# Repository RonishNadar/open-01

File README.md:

# OPEN-01

**OPEN-01** is an open-source, low-cost differential drive robot platform focused on embedded sensing, motion control, and autonomous navigation.

This repository contains the full stack:
- ESP-IDF firmware for the ESP32-S2 robot controller
- ROS2 serial bridge and bringup for Raspberry Pi 3B
- URDF robot description with STL meshes
- RViz2 visualization stack for the dev laptop
- robot_localization EKF for sensor fusion
- Linux setup scripts for both machines

---

## What this repo is

OPEN-01 is designed as a low-cost, replicable alternative to the TurtleBot3. It is built around proven hardware and a clean layered architecture — embedded-first, with ROS2 as the autonomy layer on top.

The platform is structured around two compute nodes:

- **ESP32-S2** — handles all real-time firmware: sensors, motors, odometry, and UART telemetry
- **Raspberry Pi 3B** — runs ROS2 Humble, bridges ESP32 telemetry to ROS2 topics, and relays lidar data
- **Laptop** — runs EKF, SLAM, Nav2, and RViz2 visualization over WiFi

---

## Current capabilities

### Firmware (ESP32-S2)
- **Motor control** — FIT0441 brushless DC motors, 25kHz PWM, encoder feedback, startup kick
- **IMU** — MPU6500 (WHO_AM_I=0x70), dedicated I2C bus, accel + gyro
- **ToF ranging** — 3x VL53L0X (left, right, back), XSHUT-based address assignment
- **Odometry** — wheel encoder integration, kinematics
- **Battery monitoring** — 3S Li-Ion voltage via ADC with voltage divider
- **UART telemetry** — custom binary protocol at 460800 baud with CRC16-CCITT

### ROS2 Stack (Raspberry Pi 3B — ROS2 Humble)
- **Serial bridge node** — parses ESP32 binary protocol, publishes all sensor topics
- **Lidar node** — LDS-02 lidar via USB2LDS adapter, publishes `/scan` *(in progress)*
- **robot_state_publisher** — broadcasts full TF tree from URDF
- **Systemd autostart** — `open01.service` brings up the full stack on boot

### ROS2 Stack (Laptop — ROS2 Jazzy)
- **RViz2 visualization** — CAD model, TF frames, odometry, lidar scan
- **robot_localization EKF** — fuses `/odom` + `/imu/data` → `/odometry/filtered` at 30Hz
- **SLAM Toolbox** — *(planned)*
- **Nav2** — *(planned)*

### Published ROS2 Topics
| Topic | Type | Source |
|-------|------|--------|
| `/odom` | `nav_msgs/Odometry` | Serial bridge |
| `/imu/data` | `sensor_msgs/Imu` | Serial bridge |
| `/battery_state` | `sensor_msgs/BatteryState` | Serial bridge |
| `/tof/left` | `sensor_msgs/Range` | Serial bridge |
| `/tof/right` | `sensor_msgs/Range` | Serial bridge |
| `/tof/back` | `sensor_msgs/Range` | Serial bridge |
| `/scan` | `sensor_msgs/LaserScan` | Lidar node |
| `/joint_states` | `sensor_msgs/JointState` | Serial bridge |
| `/odometry/filtered` | `nav_msgs/Odometry` | EKF node |
| `/cmd_vel` | `geometry_msgs/Twist` | Nav2 / teleop |

---

## Hardware

| Component | Part |
|-----------|------|
| Microcontroller | ESP32-S2 |
| Companion computer | Raspberry Pi 3B |
| Motors | FIT0441 brushless DC with encoders |
| IMU | MPU6500 |
| ToF sensors | 3x VL53L0X |
| Lidar | LDS-02 (via USB2LDS adapter, CP210x) |
| Battery | 3S Li-Ion (12.6V full, 9.0V cutoff) |

### Pin Map (ESP32-S2)

| Function | GPIO |
|----------|------|
| I2C Bus 0 SDA (ToF) | GPIO14 |
| I2C Bus 0 SCL (ToF) | GPIO13 |
| I2C Bus 1 SDA (IMU) | GPIO5 |
| I2C Bus 1 SCL (IMU) | GPIO4 |
| XSHUT Left (0x30) | GPIO12 |
| XSHUT Back (0x31) | GPIO11 |
| XSHUT Right (0x32) | GPIO10 |
| UART TX | GPIO19 |
| UART RX | GPIO20 |
| Motor Right PWM | GPIO15 |
| Motor Right DIR | GPIO16 |
| Motor Right FG | GPIO17 |
| Motor Left PWM | GPIO21 |
| Motor Left DIR | GPIO33 |
| Motor Left FG | GPIO34 |
| Battery ADC | GPIO2 |

---

## Repository structure

```text
open-01/
├── robot_firmware/              # ESP32-S2 firmware (ESP-IDF v5.4)
│   └── main/
│       ├── config/              # GPIO, timing, robot geometry constants
│       ├── common/              # Shared robot state
│       ├── drivers/             # MPU6500, VL53L0X, motor drivers
│       ├── hal/                 # Hardware abstraction layer
│       ├── services/            # PID, kinematics, odometry, comms
│       └── tasks/               # FreeRTOS tasks (IMU, ToF, motor, comms)
├── robot_ros2/
│   └── ros2_ws/
│       └── src/
│           ├── open01_serial_bridge/   # ESP32 <-> ROS2 bridge + lidar node
│           ├── open01_bringup/         # RPi launch files
│           ├── open01_description/     # URDF + STL meshes
│           └── open01_viz/             # Laptop RViz2 launch + EKF config
├── cad/
│   └── URDFs/                   # SolidWorks URDF export (source)
├── scripts/
│   ├── setup_rpi.sh             # One-command RPi setup
│   └── setup_laptop.sh          # One-command laptop setup
├── tools/
│   ├── launcher.py              # ESP-IDF GUI launcher
│   └── setup.sh                 # ESP-IDF toolchain setup
├── LICENSE
└── README.md
```

---

## Getting started

### RPi setup (Ubuntu 22.04 + ROS2 Humble)

```bash
git clone https://github.com/RonishNadar/open-01.git
cd open-01
sudo bash scripts/setup_rpi.sh
sudo reboot
```

### Laptop setup (Ubuntu 24.04 + ROS2 Jazzy)

```bash
git clone https://github.com/RonishNadar/open-01.git
cd open-01
sudo bash scripts/setup_laptop.sh
source ~/.bashrc
```

### Firmware setup (ESP32-S2)

```bash
chmod +x tools/setup.sh
./tools/setup.sh
python3 tools/launcher.py
```

---

## Running the robot

### On RPi (auto-starts on boot via systemd)
```bash
sudo systemctl start open01.service
sudo systemctl status open01.service
```

### Manual launch on RPi
```bash
cd ~/open-01/robot_ros2/ros2_ws
source install/setup.bash
ros2 launch open01_bringup bringup.launch.py
```

### Visualization + EKF on laptop
```bash
cd ~/open-01/robot_ros2/ros2_ws
source install/setup.bash
ros2 launch open01_viz viz.launch.py
```

### Verify topics
```bash
ros2 topic list
ros2 topic hz /odometry/filtered   # should be ~30Hz
ros2 topic hz /odom                # should be ~40Hz
ros2 topic hz /scan                # should be ~5Hz
```

### Verify TF tree
```bash
ros2 run tf2_tools view_frames
```

---

## Architecture

```
ESP32-S2 (firmware)
    |  UART 460800 baud (custom binary protocol, CRC16-CCITT)
    v
Raspberry Pi 3B (ROS2 Humble)
    |-- open01_serial_bridge  ->  /odom /imu/data /battery_state /tof/* /joint_states
    |-- lidar_node            ->  /scan
    |-- robot_state_publisher ->  /tf /tf_static
    |  WiFi (DDS, ROS_DOMAIN_ID=0)
    v
Laptop (ROS2 Jazzy)
    |-- robot_localization EKF  ->  /odometry/filtered
    |-- SLAM Toolbox            ->  /map (planned)
    |-- Nav2                    ->  autonomous navigation (planned)
    |-- RViz2                   ->  visualization
```

---

## Firmware architecture

### `config/`
Central constants: GPIO assignments, I2C/UART config, task periods, robot geometry, PID defaults.

### `common/`
Shared robot state and data structures accessed across tasks.

### `drivers/`
Low-level device drivers for MPU6500, VL53L0X, and motor control.

### `hal/`
Hardware abstraction layer separating board-specific logic from services.

### `services/`
Reusable robotics logic: PID, kinematics, odometry, motor coordination, UART comms.

### `tasks/`
FreeRTOS task entry points for periodic runtime behavior. All tasks pinned to Core 0 (ESP32-S2 is single-core).

---

## Key implementation notes

- **ESP32-S2 ADC** is 13-bit — `ADC_BITWIDTH_DEFAULT`, `BATTERY_ADC_MAX = 8191.0f`
- **FIT0441 motors** use inverted PWM (255=stop, 0=full speed), require 25kHz PWM and startup kick
- **FG pins** need 5kΩ external pull-up to 3.3V (open-collector output)
- **VL53L0X** requires full Pololu init sequence (SPAD calibration, 60+ tuning registers)
- **LDS-02 checksum** is `(~sum(bytes[0:40])) & 0xFF`, `INDEX_MAX=0xDB`
- **Serial port** on Ubuntu 22.04 RPi is `/dev/ttyS0` (not `/dev/ttyAMA0`)
- **ROS2 QoS** — RPi nodes publish `BEST_EFFORT`, set RViz2 subscriptions to match
- **EKF** — IMU orientation not fused (MPU6500 has no magnetometer), only `vyaw`, `ax`, `ay` used from IMU

---

## Project status

### Firmware
- [x] ESP-IDF firmware scaffold
- [x] Shared robot state
- [x] Motor control task + PID
- [x] IMU task (MPU6500)
- [x] ToF task (3x VL53L0X)
- [x] Odometry + kinematics
- [x] Battery monitoring
- [x] UART comms task (custom binary protocol)
- [x] Linux setup script + GUI launcher

### ROS2
- [x] Serial bridge node (ESP32 <-> ROS2)
- [~] LDS-02 lidar node *(in progress — lidar bring-up)*
- [x] URDF robot description
- [x] TF tree (all frames)
- [x] RViz2 visualization
- [x] Systemd autostart
- [x] Setup scripts (RPi + laptop)
- [x] robot_localization EKF (fusing /odom + /imu/data)
- [ ] SLAM Toolbox
- [ ] Nav2
- [ ] PID gain tuning

### Documentation
- [ ] Hardware wiring guide
- [ ] Full system bring-up docs
- [ ] Demo videos

---

## Contributing

Contributions are welcome. Good areas:

- hardware abstraction cleanup
- sensor validation and calibration
- motion control improvements
- Nav2 / SLAM configuration
- documentation and wiring diagrams
- testing utilities

When contributing:
1. keep modules focused
2. avoid hardcoding constants outside `config.h`
3. preserve the layered firmware structure
4. document any hardware assumptions clearly

---

## License

Licensed under the **Apache-2.0 License**. See [`LICENSE`](LICENSE) for details.

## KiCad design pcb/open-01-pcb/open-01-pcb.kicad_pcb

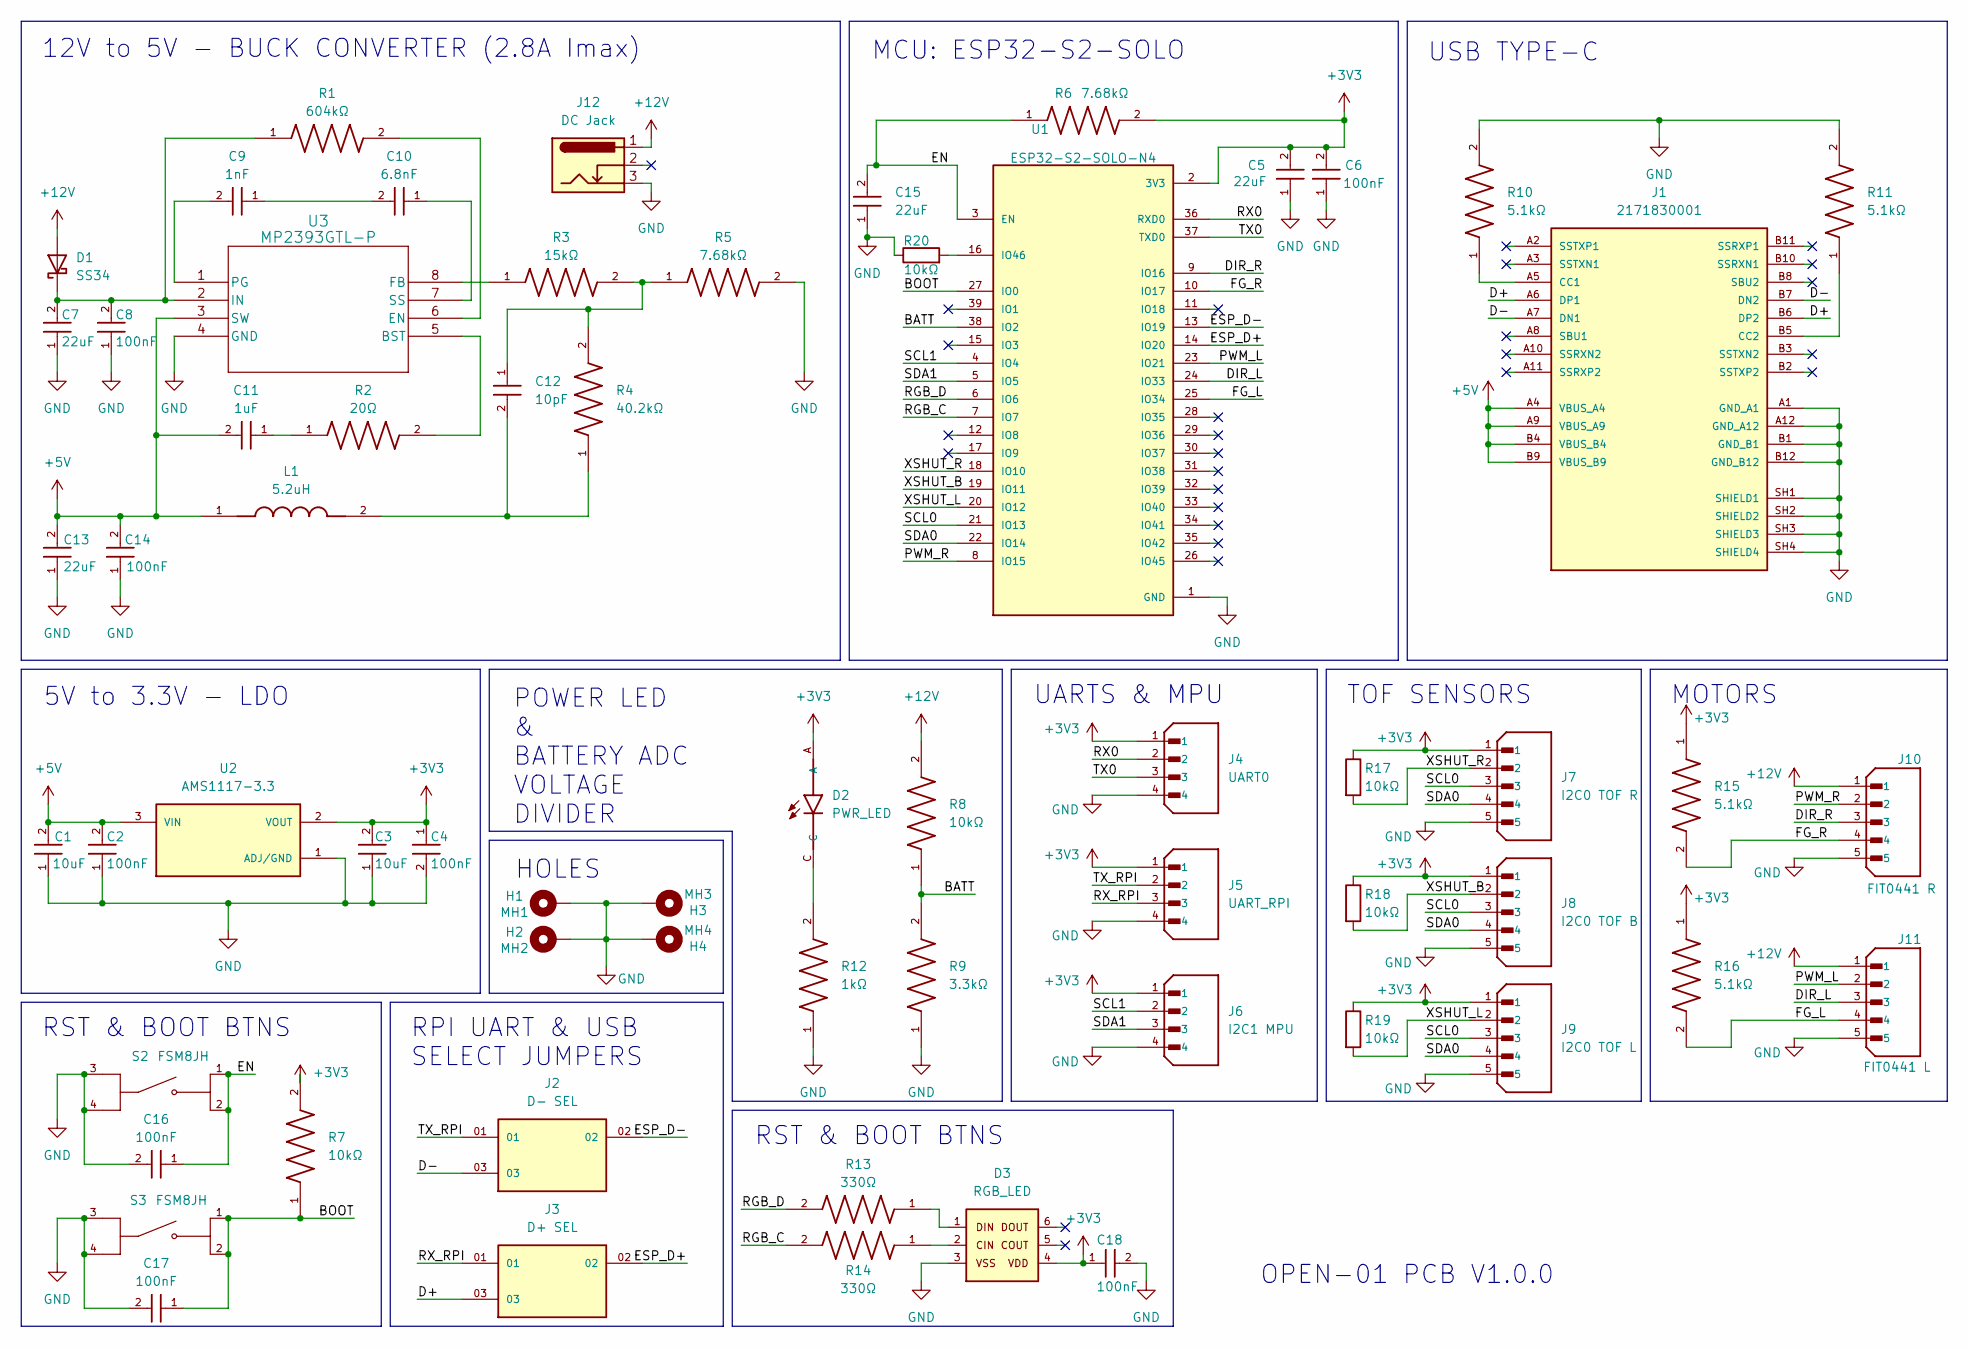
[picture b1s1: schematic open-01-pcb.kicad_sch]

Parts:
C1, C3: 10uF; WCAP-CSGP_0603_R
C2, C4, C6, C8, C14, C16, C17, C18: 100nF; WCAP-CSGP_0603_R
C5, C7, C13, C15: 22uF; WCAP-CSGP_0603_R
C9: 1nF; WCAP-CSGP_0603_R
C10: 6.8nF; WCAP-CSGP_0603_R
C11: 1uF; WCAP-CSGP_0603_R
C12: 10pF; WCAP-CSGP_0603_R
D1: SS34; D_SMA
D2: PWR_LED; LEDSC160X80X70L45N
D3: RGB_LED; WL-ILED_5050_PLCC6
H1: MH1; MountingHole_2.7mm_M2.5_Pad_Via
H2: MH2; MountingHole_2.7mm_M2.5_Pad_Via
H3: MH3; MountingHole_2.7mm_M2.5_Pad_Via
H4: MH4; MountingHole_2.7mm_M2.5_Pad_Via
J1: 2171830001; MOLEX_2171830001; PARTREV A1
J2: D- SEL; SAMTEC_TSW-101-17-T-T; PARTREV R
J3: D+ SEL; SAMTEC_TSW-101-17-T-T; PARTREV R
J4: UART0; JST_B4B-XH-A_LF__SN_; PARTREV 7/4/21
J5: UART_RPI; JST_B4B-XH-A_LF__SN_; PARTREV 7/4/21
J6: I2C1 MPU; JST_B4B-XH-A_LF__SN_; PARTREV 7/4/21
J7: I2C0 TOF R; JST_B5B-XH-A; PARTREV 7/4/21
J8: I2C0 TOF B; JST_B5B-XH-A; PARTREV 7/4/21
J9: I2C0 TOF L; JST_B5B-XH-A; PARTREV 7/4/21
J10: FIT0441 R; JST_B5B-XH-A; PARTREV 7/4/21
J11: FIT0441 L; JST_B5B-XH-A; PARTREV 7/4/21
J12: DC Jack; BarrelJack_GCT_DCJ200-10-A_Horizontal
L1: 5.2uH; IND_MSS1038-522NLC; PARTREV 09/27/22
R1: 604kΩ; RES_ERJU03J106V; PARTREV 3/1/2020
R2: 20Ω; RES_ERJU03J106V; PARTREV 3/1/2020
R3: 15kΩ; RES_ERJU03J106V; PARTREV 3/1/2020
R4: 40.2kΩ; RES_ERJU03J106V; PARTREV 3/1/2020
R5, R6: 7.68kΩ; RES_ERJU03J106V; PARTREV 3/1/2020
R7, R8: 10kΩ; RES_ERJU03J106V; PARTREV 3/1/2020
R9: 3.3kΩ; RES_ERJU03J106V; PARTREV 3/1/2020
R10, R11, R15, R16: 5.1kΩ; RES_ERJU03J106V; PARTREV 3/1/2020
R12: 1kΩ; RES_ERJU03J106V; PARTREV 3/1/2020
R13, R14: 330Ω; RES_ERJU03J106V; PARTREV 3/1/2020
R17, R18, R19, R20: 10kΩ; R_0201_0603Metric
S2, S3: FSM8JH; SW_FSM8JH; PARTREV 8-1773450-9
U1: ESP32-S2-SOLO-N4; XCVR_ESP32-S2-SOLO-N4; PARTREV 1.6
U2: AMS1117-3.3; SOT229P700X180-4N; PARTREV NA
U3: MP2393GTL-P; SOT583_MP2393

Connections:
+3V3: C3.2, C4.1, C5.2, C6.2, C18.1, D2.A, D3.4, J4.1, J5.1, J6.1, J7.1, J8.1, J9.1, R6.2, R7.2, R15.1, R16.1, R17.1, R18.1, R19.1, U1.2 (3V3), U2.2 (VOUT)
+5V: C1.2, C2.2, C11.2, C13.2, C14.2, J1.A4 (VBUS_A4), J1.A9 (VBUS_A9), J1.B4 (VBUS_B4), J1.B9 (VBUS_B9), L1.1, U2.3 (VIN), U3.3 (SW)
+12V: D1.2 (A), J10.1, J11.1, J12.1, R8.2
/BATT: R8.1, R9.2, U1.38 (IO2)
/BOOT: C17.1, R7.1, S3.1, S3.2, U1.27 (IO0)
/D+: J1.A6 (DP1), J1.B6 (DP2), J3.03
/D-: J1.A7 (DN1), J1.B7 (DN2), J2.03
/DIR_L: J11.3, U1.24 (IO33)
/DIR_R: J10.3, U1.9 (IO16)
/EN: C15.2, C16.1, R6.1, S2.1, S2.2, U1.3 (EN)
/ESP_D+: J3.02, U1.14 (IO20)
/ESP_D-: J2.02, U1.13 (IO19)
/FG_L: J11.4, R16.2, U1.25 (IO34)
/FG_R: J10.4, R15.2, U1.10 (IO17)
/PWM_L: J11.2, U1.23 (IO21)
/PWM_R: J10.2, U1.8 (IO15)
/RGB_C: R14.2, U1.7 (IO7)
/RGB_D: R13.2, U1.6 (IO6)
/RX0: J4.2, U1.36 (RXD0)
/RX_RPI: J3.01, J5.3
/SCL0: J7.3, J8.3, J9.3, U1.21 (IO13)
/SCL1: J6.2, U1.4 (IO4)
/SDA0: J7.4, J8.4, J9.4, U1.22 (IO14)
/SDA1: J6.3, U1.5 (IO5)
/TX0: J4.3, U1.37 (TXD0)
/TX_RPI: J2.01, J5.2
/XSHUT_B: J8.2, R18.2, U1.19 (IO11)
/XSHUT_L: J9.2, R19.2, U1.20 (IO12)
/XSHUT_R: J7.2, R17.2, U1.18 (IO10)
GND: C1.1, C2.1, C3.1, C4.2, C5.1, C6.1, C7.1, C8.1, C13.1, C14.1, C15.1, C16.2, C17.2, C18.2, D3.3, H1.1 (1_1), H2.1 (1_1), H3.1 (1_1), H4.1 (1_1), J1.A1 (GND_A1), J1.A12 (GND_A12), J1.B1 (GND_B1), J1.B12 (GND_B12), J1.SH1 (SHIELD1), J1.SH2 (SHIELD2), J1.SH3 (SHIELD3), J1.SH4 (SHIELD4), J4.4, J5.4, J6.4, J7.5, J8.5, J9.5, J10.5, J11.5, J12.3, R5.2, R9.1, R10.2, R11.2, R12.1, R20.1, S2.3, S2.4, S3.3, S3.4, U1.1 (GND), U1.40 (GND), U1.41_1 (GND), U1.41_2 (GND), U1.41_3 (GND), U1.41_4 (GND), U1.41_5 (GND), U1.41_6 (GND), U1.41_7 (GND), U1.41_8 (GND), U1.41_9 (GND), U2.1 (ADJ/GND), U3.4 (GND)
unnamed: C9.1, C10.2
unnamed: C11.1, R2.1
unnamed: C12.1, R3.2, R4.2, R5.1
unnamed: C12.2, L1.2, R4.1
unnamed: C7.2, C8.2, D1.1 (K), R1.1, U3.2 (IN)
unnamed: D2.C, R12.2
unnamed: D3.1, R13.1
unnamed: D3.2, R14.1
unnamed: J1.A5 (CC1), R10.1
unnamed: J1.B5 (CC2), R11.1
unnamed: R20.2, U1.16 (IO46)
unnamed: R2.2, U3.5 (BST)
unnamed: R1.2, U3.6 (EN)
unnamed: R3.1, U3.8 (FB)
unnamed: C9.2, U3.1 (PG)
unnamed: C10.1, U3.7 (SS)

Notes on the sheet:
RPI UART & USB SELECT JUMPERS
OPEN-01 PCB V1.0.0
RST & BOOT BTNS
POWER LED & BATTERY ADC VOLTAGE DIVIDER
12V to 5V - BUCK CONVERTER (2.8A Imax)
MOTORS
HOLES
MCU: ESP32-S2-SOLO
UARTS & MPU
TOF SENSORS
5V to 3.3V - LDO
USB TYPE-C

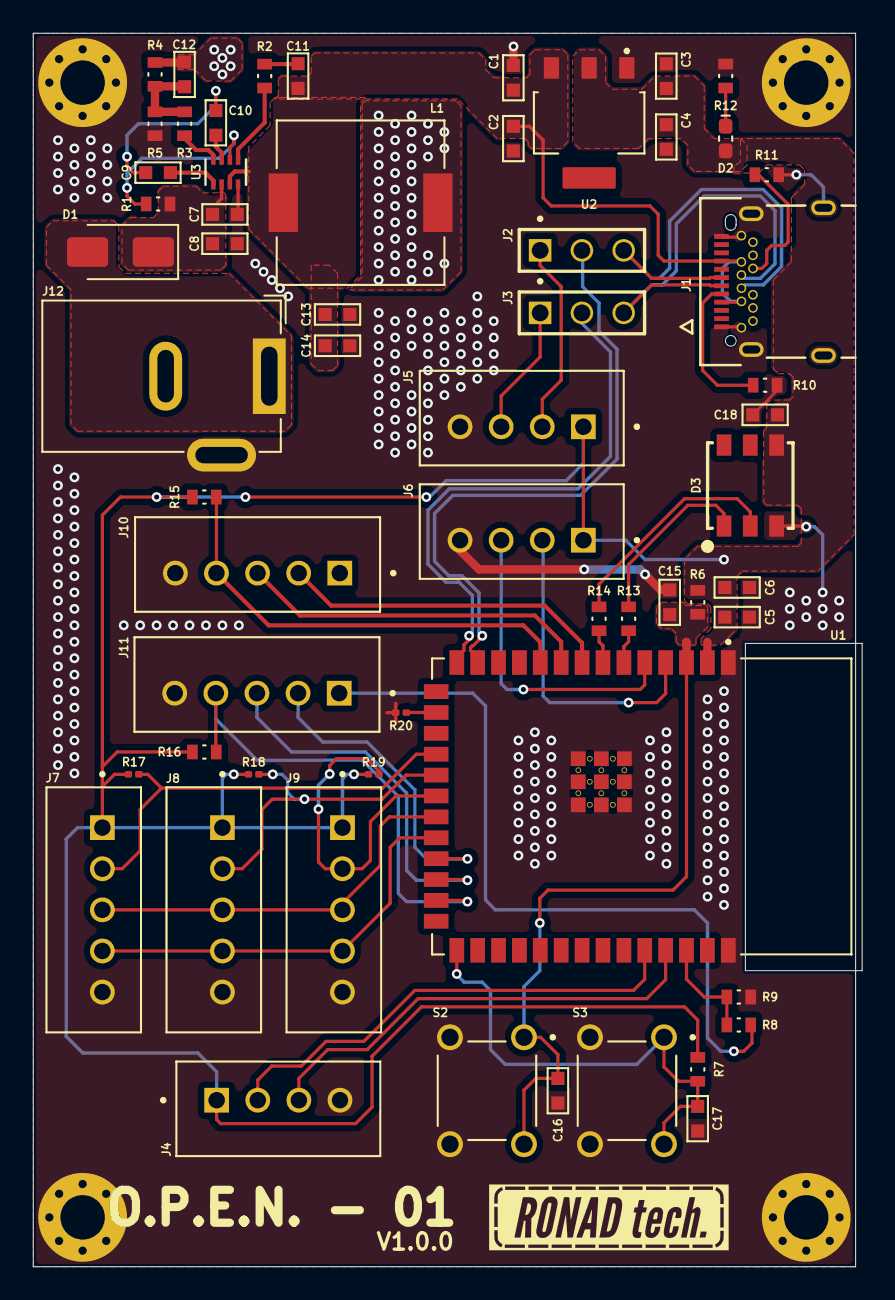
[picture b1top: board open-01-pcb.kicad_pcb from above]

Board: 2 copper layers, 50.0 x 75.0 mm, 63 parts (0 on the bottom side), 46 nets.

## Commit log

2026-03-25 Add motor controller, odometry, and PID controller implementations
    - Implemented motor_controller.h and motor_controller.cpp for velocity PID control and odometry integration.
    - Created odometry.h and odometry.cpp for wheel odometry pose integration.
    - Added pid.h and pid.cpp for a generic PID controller implementation.
    - Developed task_motor and task_imu for motor control and IMU data handling.
    - Introduced task_tof for time-of-flight sensor data processing.
    - Added setup script and GUI launcher for ESP-IDF project management.
2026-03-25 Update README.md to reflect current project structure, capabilities, and setup instructions
2026-03-25 Update README to reflect current project details
    Removed outdated project description and added a concise overview of the OPEN-01 robotics platform.
2026-03-25 Add battery monitoring functionality and related components
2026-03-25 Mark battery monitoring task as completed
2026-03-27 feat: Implement communication handling and telemetry
    - Added comms task to manage UART communication and telemetry data transmission.
    - Introduced comm_handler for processing incoming commands and building telemetry packets.
    - Enhanced robot_state to include command velocity and emergency stop functionalities.
    - Updated CMakeLists to include new comms and task_comms files.
    - Refactored motor task to respond to command velocities and emergency stop signals.
    - Created comm_serial for UART communication setup and data handling.
2026-03-27 Remove unused micro-ROS submodule reference
    micro-ROS is not used in the project. Removes the .gitmodules entry
    and updates the misleading comment in config.h that referenced it.
    https://claude.ai/code/session_011CtqKdB1EYpvDsfjvLoJEe
2026-03-28 feat: Enhance motor control and communication logging
    - Added I2C bus recovery mechanism in drv_mpu6500.cpp
    - Improved motor initialization in hal_motor.cpp with ISR setup
    - Introduced hal_motor_debug_delta function for motor delta tracking
    - Updated command velocity logging in comm_handler.cpp and task_motor.cpp
    - Adjusted CMakeLists.txt to include necessary dependencies
    - Refactored config.h for better organization of motor constants
2026-03-28 feat: Add initial implementation of open01_bringup and open01_serial_bridge packages
2026-03-28 feat: Add ROS2 serial bridge node and bringup package
2026-03-28 feat: Add LDS-02 lidar node and unified bringup launch
2026-03-29 fix: use ttyS0 for ESP32 UART, ttyLIDAR udev rule for LDS-02
2026-03-29 fix: remove lidar from bringup, serial bridge only
2026-03-29 feat: autostart service, OLED status display, boot optimisation
2026-03-29 feat: implement cold-start recovery mechanism in motor task
2026-03-29 feat: Add URDF model and description package for OPEN-01
    - Added Robot_Assembly_1.urdf defining robot structure with base_link, wheels, IMU, and TOF sensor links.
    - Included STL mesh files for base_link, left/right wheels, IMU, and TOF sensors (left, right, back).
    - Created display.launch for visualizing the robot model in RViz.
    - Added gazebo.launch for simulating the robot in Gazebo.
    - Added package.xml with package metadata and dependencies for the description package.
    - Included Robot_Assembly_1.csv for additional robot configuration data.
2026-03-29 feat: Add URDF and launch files for Robot Assembly 1
    - Created display.launch and gazebo.launch files to facilitate visualization and simulation of the Robot Assembly 1.
    - Added URDF model (Robot_Assembly_1.urdf) and associated meshes for the robot components including wheels, IMU, and TOF sensors.
    - Introduced a CSV file for the robot's link properties and a Python script for testing serial communication with the sensor.
    - Updated package.xml to include necessary dependencies for the new robot description package.
2026-03-29 feat: Add open01_description ROS2 package with URDF model
    - Added open01.urdf defining robot structure with base_link, wheels, IMU, and TOF sensor links.
    - Migrated package from ROS1 catkin to ROS2 ament_cmake build system.
    - Updated CMakeLists.txt and package.xml for ROS2 compatibility.
    - Renamed all Robot_Assembly_1 references to open01_description.
    - Added joint_names_open01.yaml for joint configuration.
    - Updated .gitignore to exclude ROS2 build artifacts.
2026-03-29 feat: Publish /joint_states from wheel odometry in serial bridge
    - Added JointState publisher to serial_bridge_node for Left_Wheel and Right_Wheel.
    - Integrated wheel position from linear and angular velocity using wheel geometry.
    - Added WHEEL_BASE and WHEEL_RADIUS constants derived from URDF joint origins.
    - Updated bringup.launch.py to include robot_state_publisher with publish_frequency.
2026-03-30 fix: Remove empty IMU mesh, lowercase STL extensions in URDF
2026-03-30 fix: Update URDF colors for OPEN-01
2026-03-30 feat: Add setup scripts for RPi and laptop
2026-03-30 feat: Add visualization launch package for OPEN-01 with URDF and RViz configuration
2026-03-30 docs: Update README.md to enhance project description and capabilities
2026-03-30 feat: Add EKF configuration and node to launch file for robot localization
2026-03-30 docs: Update README.md to include detailed EKF functionality and topic verification
2026-03-30 feat: Add OPEN-01 Dashboard with enhanced UI and telemetry features
2026-04-05 feat(hardware): Add OPEN-01 PCB V1.0.0 initial design
    - ESP32-S2-SOLO-2 as main MCU with USB OTG programming interface
    - MP2393 buck converter (12V → 5V/3A) for Raspberry Pi power
    - AMS1117-3.3 LDO (5V → 3.3V) for MCU and sensor rail
    - SS34 Schottky diode for reverse polarity protection on VBAT
    - VL53L0X ToF sensors x3 (left, back, right) with XSHUT addressing
    - MPU6500 IMU on dedicated I2C bus 1
2026-04-05 chore: Remove history submodule for open-01 PCB
2026-04-05 chore: Add initial STEP file for PCB design version 1.0.0
2026-04-09 Revert "Remove unused micro-ROS submodule reference"
    This reverts commit 83920757b3a313bf5224923ef2108fb88f04f1c2.
